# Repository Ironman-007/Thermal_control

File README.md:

# Thermal_control

Due to my research, I always need to measure, log, and control the temperature of the environment during some experiment, such as TVAC test, etc. So I think it would be great to have a standard Kit to do this.
I made this for my personal usage, with 4 channels of RTD to measure temeprature and 4 channels of heater control.

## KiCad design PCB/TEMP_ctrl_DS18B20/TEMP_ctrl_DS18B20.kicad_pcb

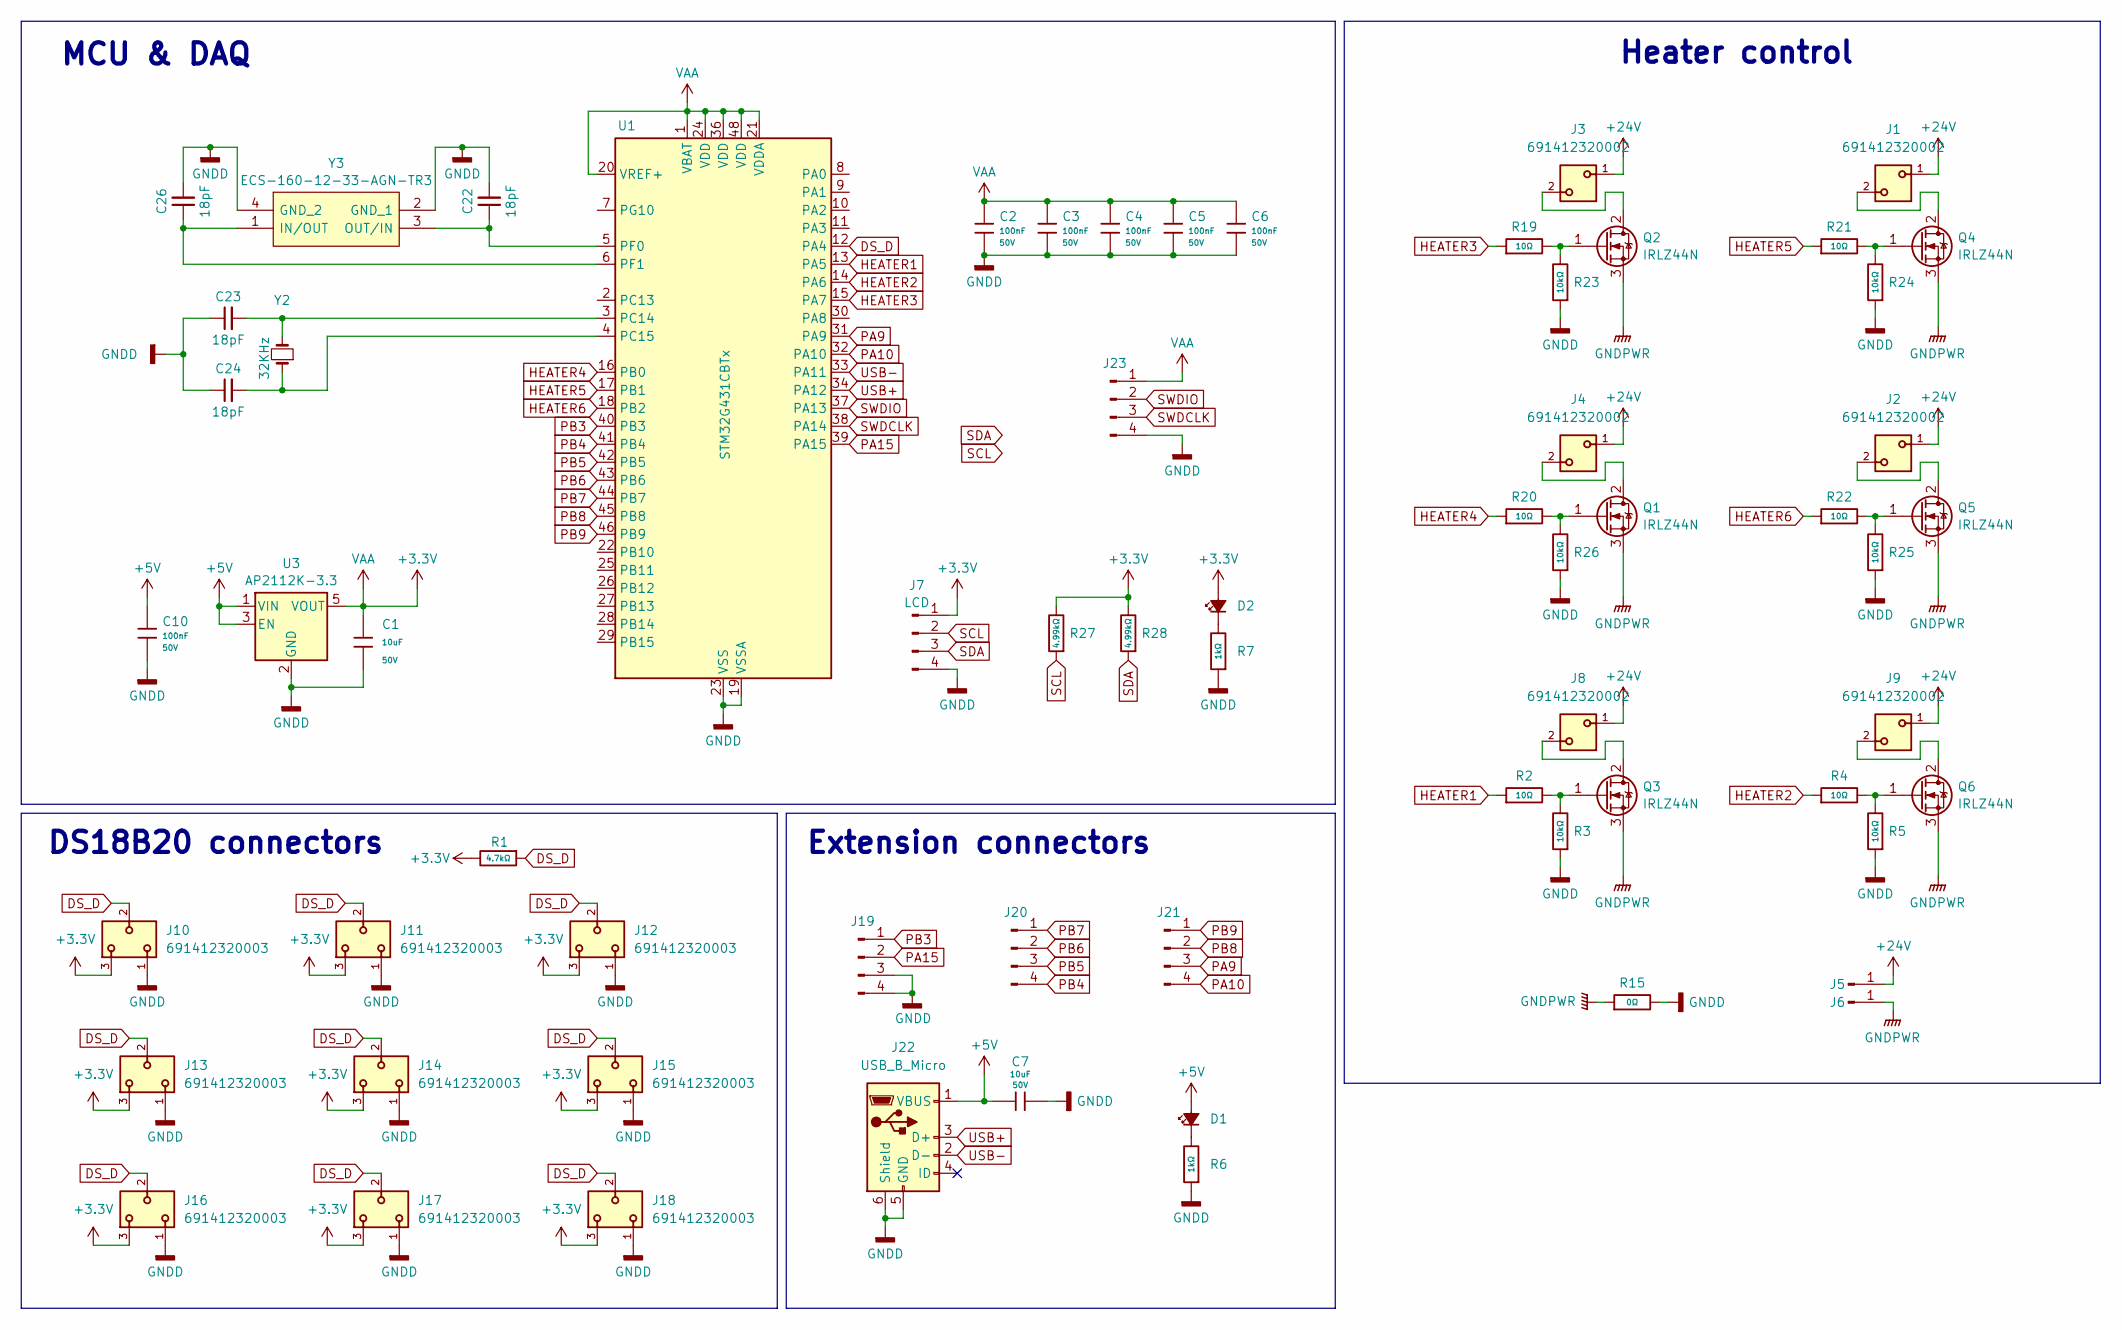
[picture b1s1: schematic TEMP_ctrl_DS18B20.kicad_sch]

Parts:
C1, C7: 10uF; C_1206; Voltage Rated 50V; Tolerance ±10%; Part CL31B104KBCNNNC; LCSC C24497
C2, C3, C4, C5, C6, C10: 100nF; C_0603_1608Metric; Voltage Rated 50V; Tolerance ±10%; Part CL31B104KBCNNNC; LCSC C24497
C22, C23, C24, C26: 18pF; C_0402_1005Metric_Pad0.74x0.62mm_HandSolder
D1, D2: LED_Small_Filled; LED_1206_3216Metric
J1, J2, J3, J4, J8, J9: 691412320002
J5, J6: Conn_01x01_Pin; TestPoint_Pad_4.0x4.0mm
J7: LCD; PinHeader_1x04_P2.54mm_Vertical
J10, J11, J12, J13, J14, J15, J16, J17, J18: 691412320003
J19, J20, J21, J23: Conn_01x04_Pin; PinHeader_1x04_P2.54mm_Vertical
J22: USB_B_Micro; USB_Micro-B_Amphenol_10104110_Horizontal
Q1, Q2, Q3, Q4, Q5, Q6: IRLZ44N; TO-220-3_Vertical
R1: 4.7kΩ; R_1206; Overload Voltage (Max) 200V; Tolerance ±1%; Part 1206W4F1001T5E; LCSC C4410
R2, R4, R19, R20, R21, R22: 10Ω; R_1206; Overload Voltage (Max) 200V; Tolerance ±1%; Part 1206W4F1001T5E; LCSC C4410
R3, R5, R23, R24, R25, R26: 10kΩ; R_1206; Overload Voltage (Max) 200V; Tolerance ±1%; Part 1206W4F1001T5E; LCSC C4410
R6, R7: 1kΩ; R_1206; Overload Voltage (Max) 200V; Tolerance ±1%; Part 1206W4F1001T5E; LCSC C4410
R15: 0Ω; R_1206; Overload Voltage (Max) 200V; Tolerance ±1%; Part 1206W4F0000T5E; LCSC C17888
R27, R28: 4.99kΩ; R_1206; Overload Voltage (Max) 200V; Tolerance ±1%; Part 1206W4F1001T5E; LCSC C4410
U1: STM32G431CBTx; LQFP-48_7x7mm_P0.5mm
U3: AP2112K-3.3; SOT-23-5
Y2: 32KHz; Crystal_SMD_3215-2Pin_3.2x1.5mm
Y3: ECS-160-12-33-AGN-TR3; XTAL_ECS-160-12-33-AGN-TR3; Manufacturer_Part_Number ECS-160-12-33-AGN-TR3; Mouser Part Number 520-160-12-33AGN-TR3

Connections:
+3.3V: C1.1, C2.1, C3.1, C4.1, C5.1, C6.1, D2.2 (A), J7.1, J10.3, J11.3, J12.3, J13.3, J14.3, J15.3, J16.3, J17.3, J18.3, J23.1, R1.2, R27.2, R28.2, U1.1 (VBAT), U1.20 (VREF+), U1.21 (VDDA), U1.24 (VDD), U1.36 (VDD), U1.48 (VDD), U3.5 (VOUT)
+5V: C7.1, C10.1, D1.2 (A), J22.1 (VBUS), U3.1 (VIN), U3.3 (EN)
+24V: J1.1, J2.1, J3.1, J4.1, J5.1, J8.1, J9.1
DS_D: J10.2, J11.2, J12.2, J13.2, J14.2, J15.2, J16.2, J17.2, J18.2, R1.1, U1.12 (PA4)
GNDD: C1.2, C2.2, C3.2, C4.2, C5.2, C6.2, C7.2, C10.2, C22.2, C23.1, C24.1, C26.2, J7.4, J10.1, J11.1, J12.1, J13.1, J14.1, J15.1, J16.1, J17.1, J18.1, J19.3, J19.4, J22.5 (GND), J22.6 (Shield), J23.4, R3.1, R5.1, R6.1, R7.1, R15.2, R23.1, R24.1, R25.1, R26.1, U1.19 (VSSA), U1.23 (VSS), U1.35 (VSS), U1.47 (VSS), U3.2 (GND), Y3.2 (GND_1), Y3.4 (GND_2)
GNDPWR: J6.1, Q1.3 (S), Q2.3 (S), Q3.3 (S), Q4.3 (S), Q5.3 (S), Q6.3 (S), R15.1
HEATER1: R2.1, U1.13 (PA5)
HEATER2: R4.1, U1.14 (PA6)
HEATER3: R19.1, U1.15 (PA7)
HEATER4: R20.1, U1.16 (PB0)
HEATER5: R21.1, U1.17 (PB1)
HEATER6: R22.1, U1.18 (PB2)
unnamed: D1.1 (K), R6.2
unnamed: D2.1 (K), R7.2
unnamed: J4.2, Q1.2 (D)
unnamed: Q1.1 (G), R20.2, R26.2
unnamed: J3.2, Q2.2 (D)
unnamed: Q2.1 (G), R19.2, R23.2
unnamed: J8.2, Q3.2 (D)
unnamed: Q3.1 (G), R2.2, R3.2
unnamed: J1.2, Q4.2 (D)
unnamed: Q4.1 (G), R21.2, R24.2
unnamed: J2.2, Q5.2 (D)
unnamed: Q5.1 (G), R22.2, R25.2
unnamed: J9.2, Q6.2 (D)
unnamed: Q6.1 (G), R4.2, R5.2
unnamed: C23.2, U1.3 (PC14), Y2.2
unnamed: C24.2, U1.4 (PC15), Y2.1
unnamed: C22.1, U1.5 (PF0), Y3.3 (OUT/IN)
unnamed: C26.1, U1.6 (PF1), Y3.1 (IN/OUT)
PA9: J21.3, U1.31 (PA9)
PA10: J21.4, U1.32 (PA10)
PA15: J19.2, U1.39 (PA15)
PB3: J19.1, U1.40 (PB3)
PB4: J20.4, U1.41 (PB4)
PB5: J20.3, U1.42 (PB5)
PB6: J20.2, U1.43 (PB6)
PB7: J20.1, U1.44 (PB7)
PB8: J21.2, U1.45 (PB8)
PB9: J21.1, U1.46 (PB9)
SCL: J7.2, R27.1
SDA: J7.3, R28.1
SWDCLK: J23.3, U1.38 (PA14)
SWDIO: J23.2, U1.37 (PA13)
USB+: J22.3 (D+), U1.34 (PA12)
USB-: J22.2 (D-), U1.33 (PA11)

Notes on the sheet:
Heater control
DS18B20 connectors
Extension connectors
MCU & DAQ

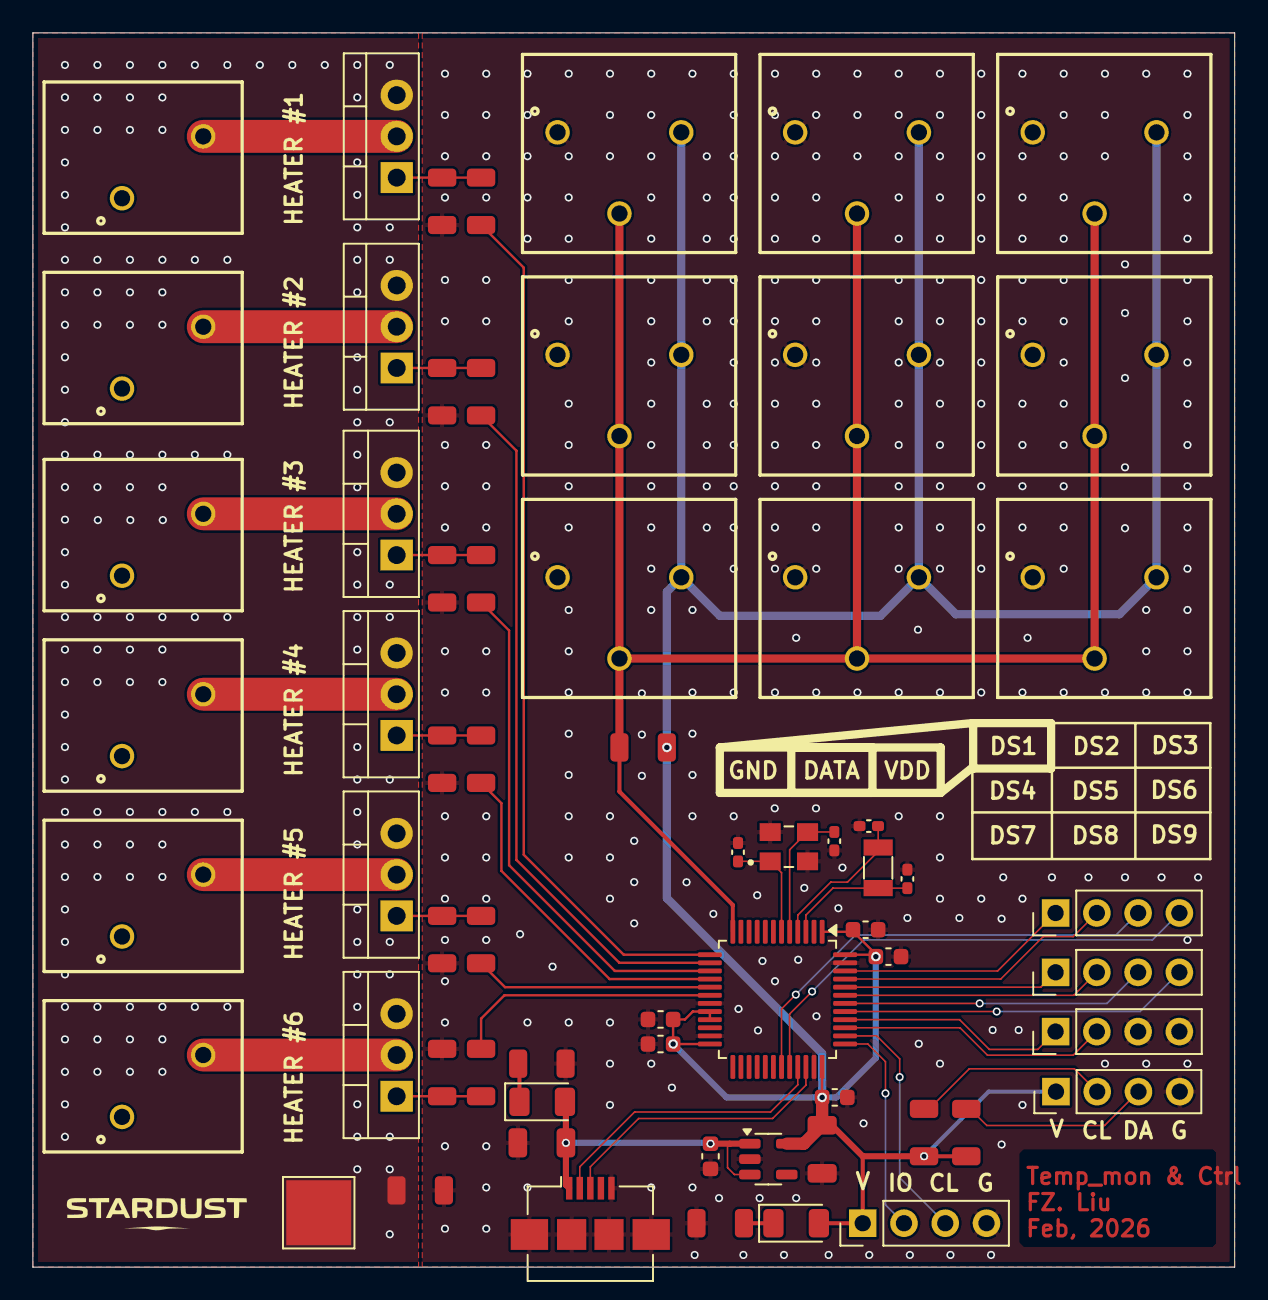
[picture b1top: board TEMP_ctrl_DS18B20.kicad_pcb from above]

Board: 2 copper layers, 74.0 x 76.0 mm, 65 parts (1 on the bottom side), 46 nets.

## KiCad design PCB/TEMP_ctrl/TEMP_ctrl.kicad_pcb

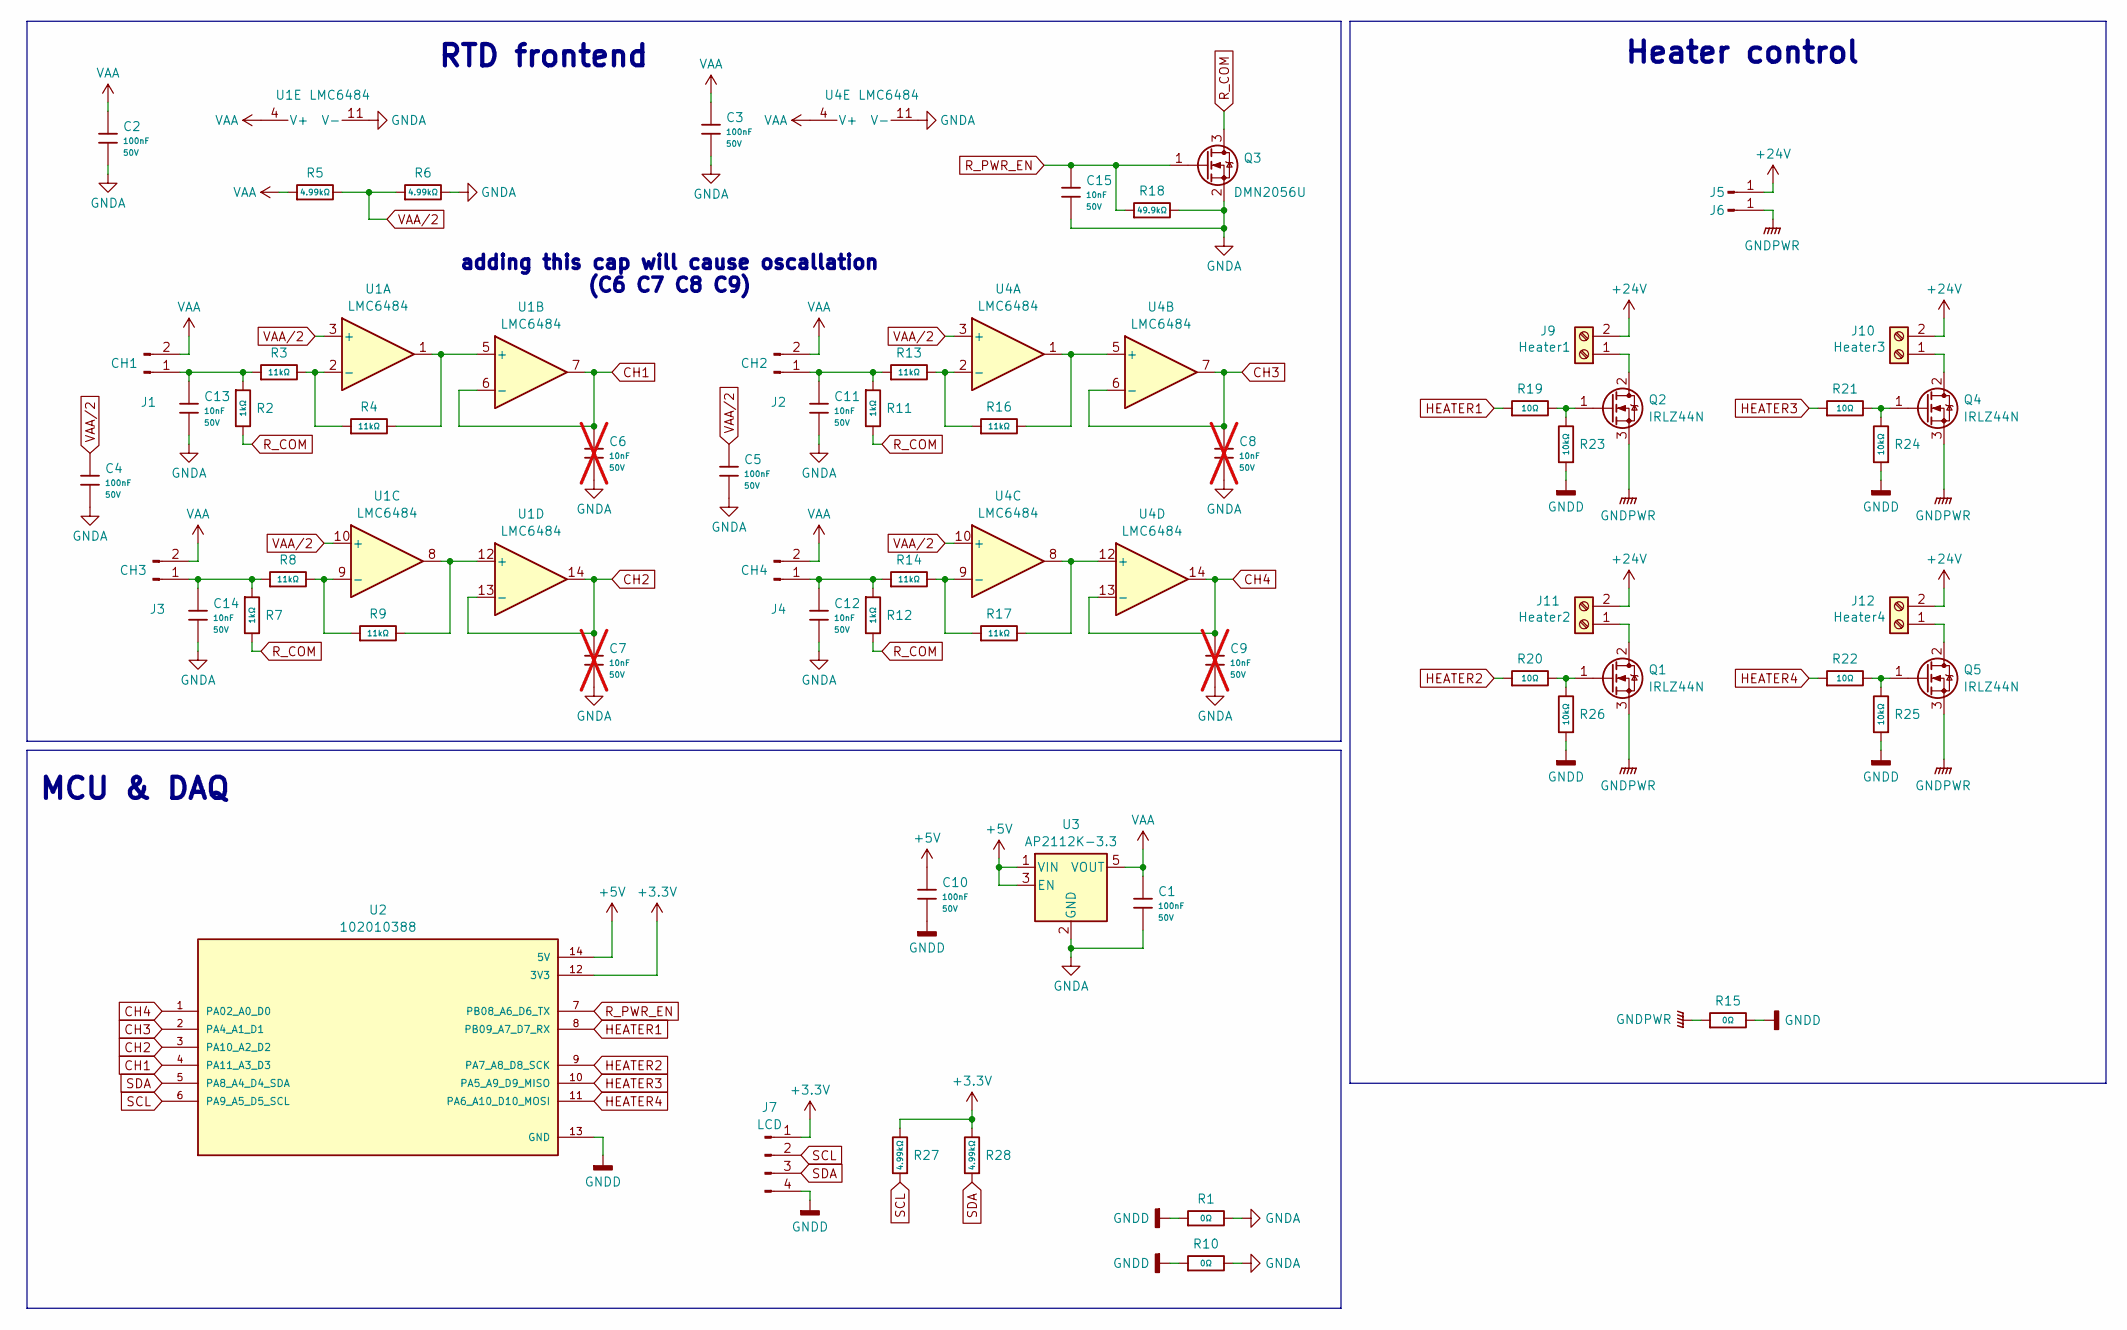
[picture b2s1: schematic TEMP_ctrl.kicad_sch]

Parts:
C1, C2, C3, C4, C5, C10: 100nF; C_1206; Voltage Rated 50V; Tolerance ±10%; Part CL31B104KBCNNNC; LCSC C24497
C6, C7, C8, C9: 10nF; C_1206; Voltage Rated 50V; Tolerance ±10%; Part CL31B104KBCNNNC; LCSC C24497; not fitted
C11, C12, C13, C14, C15: 10nF; C_1206; Voltage Rated 50V; Tolerance ±10%; Part CL31B104KBCNNNC; LCSC C24497
J1: CH1; TerminalBlock_Xinya_XY308-2.54-2P_1x02_P2.54mm_Horizontal
J2: CH2; TerminalBlock_Xinya_XY308-2.54-2P_1x02_P2.54mm_Horizontal
J3: CH3; TerminalBlock_Xinya_XY308-2.54-2P_1x02_P2.54mm_Horizontal
J4: CH4; TerminalBlock_Xinya_XY308-2.54-2P_1x02_P2.54mm_Horizontal
J5, J6: Conn_01x01_Pin; TestPoint_Pad_4.0x4.0mm
J7: LCD; PinHeader_1x04_P2.54mm_Vertical
J9: Heater1; TerminalBlock_MaiXu_MX126-5.0-02P_1x02_P5.00mm
J10: Heater3; TerminalBlock_MaiXu_MX126-5.0-02P_1x02_P5.00mm
J11: Heater2; TerminalBlock_MaiXu_MX126-5.0-02P_1x02_P5.00mm
J12: Heater4; TerminalBlock_MaiXu_MX126-5.0-02P_1x02_P5.00mm
Q1, Q2, Q4, Q5: IRLZ44N; TO-220-3_Vertical
Q3: DMN2056U; SOT-23
R1, R10, R15: 0Ω; R_1206; Overload Voltage (Max) 200V; Tolerance ±1%; Part 1206W4F0000T5E; LCSC C17888
R2, R7, R11, R12: 1kΩ; R_1206; Overload Voltage (Max) 200V; Tolerance ±1%; Part 1206W4F1001T5E; LCSC C4410
R3, R4, R8, R9, R13, R14, R16, R17: 11kΩ; R_1206; Overload Voltage (Max) 200V; Tolerance ±1%; Part 1206W4F1001T5E; LCSC C4410
R5, R6, R27, R28: 4.99kΩ; R_1206; Overload Voltage (Max) 200V; Tolerance ±1%; Part 1206W4F1001T5E; LCSC C4410
R18: 49.9kΩ; R_1206; Overload Voltage (Max) 200V; Tolerance ±1%; Part 1206W4F1001T5E; LCSC C4410
R19, R20, R21, R22: 10Ω; R_1206; Overload Voltage (Max) 200V; Tolerance ±1%; Part 1206W4F1001T5E; LCSC C4410
R23, R24, R25, R26: 10kΩ; R_1206; Overload Voltage (Max) 200V; Tolerance ±1%; Part 1206W4F1001T5E; LCSC C4410
U1, U4: LMC6484; SOIC-14_L8.7-W3.9-P1.27-LS6.0-BL
U2: 102010388; MODULE_102010388; PARTREV N/A
U3: AP2112K-3.3; SOT-23-5

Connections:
+3.3V: J7.1, R27.2, R28.2, U2.12 (3V3)
+5V: C10.1, U2.14 (5V), U3.1 (VIN), U3.3 (EN)
+24V: J5.1, J9.2, J10.2, J11.2, J12.2
CH1: C6.1, U1.6 (-), U1.7, U2.4 (PA11_A3_D3)
CH2: C7.1, U1.13 (-), U1.14, U2.3 (PA10_A2_D2)
CH3: C8.1, U2.2 (PA4_A1_D1), U4.6 (-), U4.7
CH4: C9.1, U2.1 (PA02_A0_D0), U4.13 (-), U4.14
GNDA: C1.2, C2.2, C3.2, C4.2, C5.2, C6.2, C7.2, C8.2, C9.2, C11.2, C12.2, C13.2, C14.2, C15.2, Q3.2 (S), R1.2, R6.2, R10.2, R18.2, U1.11 (V-), U3.2 (GND), U4.11 (V-)
GNDD: C10.2, J7.4, R1.1, R10.1, R15.2, R23.1, R24.1, R25.1, R26.1, U2.13 (GND)
GNDPWR: J6.1, Q1.3 (S), Q2.3 (S), Q4.3 (S), Q5.3 (S), R15.1
HEATER1: R19.1, U2.8 (PB09_A7_D7_RX)
HEATER2: R20.1, U2.9 (PA7_A8_D8_SCK)
HEATER3: R21.1, U2.10 (PA5_A9_D9_MISO)
HEATER4: R22.1, U2.11 (PA6_A10_D10_MOSI)
unnamed: C13.1, J1.1, R2.1, R3.1
unnamed: C11.1, J2.1, R11.1, R13.1
unnamed: C14.1, J3.1, R7.1, R8.1
unnamed: C12.1, J4.1, R12.1, R14.1
unnamed: J9.1, Q2.2 (D)
unnamed: J10.1, Q4.2 (D)
unnamed: J11.1, Q1.2 (D)
unnamed: J12.1, Q5.2 (D)
unnamed: Q1.1 (G), R20.2, R26.2
unnamed: Q2.1 (G), R19.2, R23.2
unnamed: Q4.1 (G), R21.2, R24.2
unnamed: Q5.1 (G), R22.2, R25.2
unnamed: R3.2, R4.1, U1.2 (-)
unnamed: R4.2, U1.1, U1.5 (+)
unnamed: R8.2, R9.1, U1.9 (-)
unnamed: R9.2, U1.8, U1.12 (+)
unnamed: R13.2, R16.1, U4.2 (-)
unnamed: R16.2, U4.1, U4.5 (+)
unnamed: R14.2, R17.1, U4.9 (-)
unnamed: R17.2, U4.8, U4.12 (+)
R_COM: Q3.3 (D), R2.2, R7.2, R11.2, R12.2
R_PWR_EN: C15.1, Q3.1 (G), R18.1, U2.7 (PB08_A6_D6_TX)
SCL: J7.2, R27.1, U2.6 (PA9_A5_D5_SCL)
SDA: J7.3, R28.1, U2.5 (PA8_A4_D4_SDA)
VAA: C1.1, C2.1, C3.1, J1.2, J2.2, J3.2, J4.2, R5.1, U1.4 (V+), U3.5 (VOUT), U4.4 (V+)
VAA/2: C4.1, C5.1, R5.2, R6.1, U1.3 (+), U1.10 (+), U4.3 (+), U4.10 (+)

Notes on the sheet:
Heater control
RTD frontend
adding this cap will cause oscallation (C6 C7 C8 C9)
MCU & DAQ

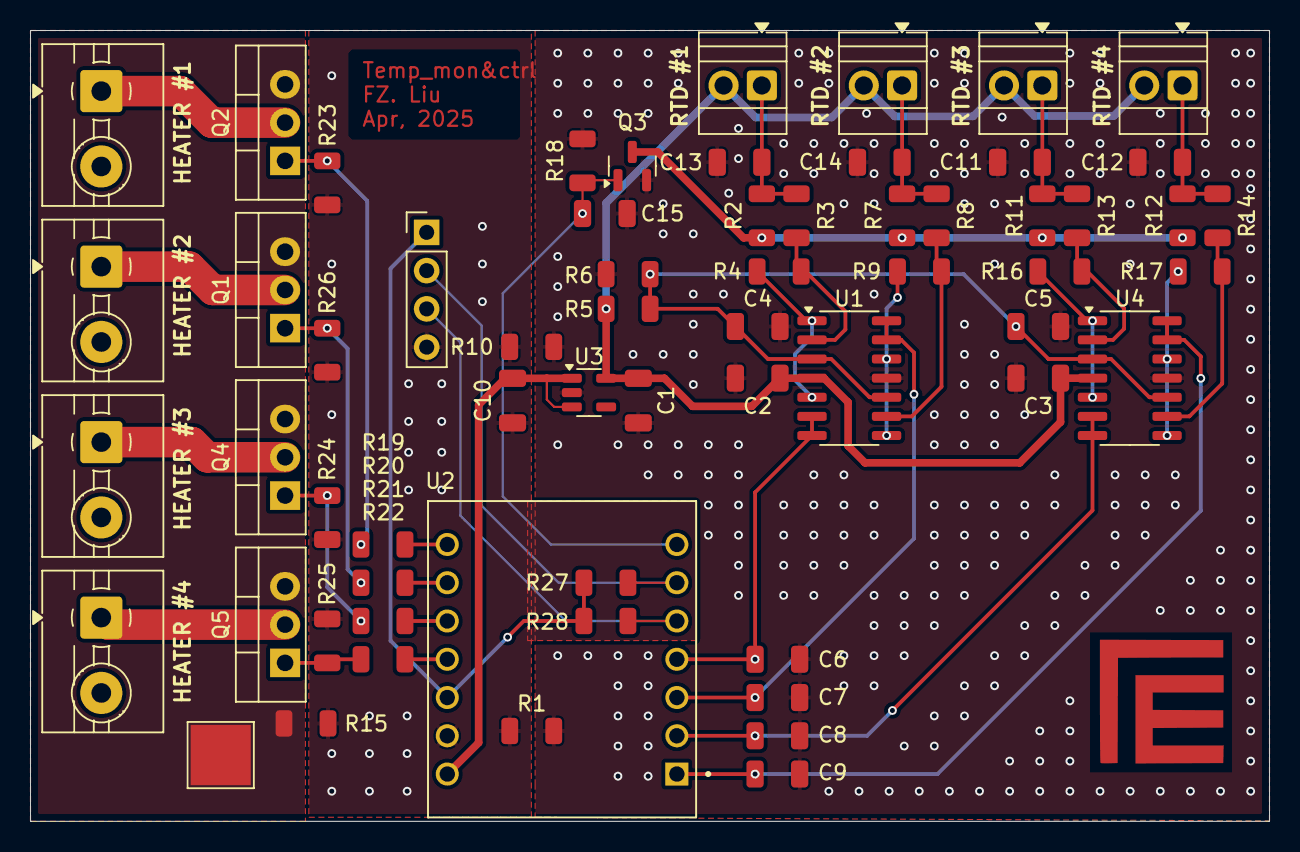
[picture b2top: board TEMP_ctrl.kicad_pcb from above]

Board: 2 copper layers, 82.2 x 52.5 mm, 63 parts (1 on the bottom side), 40 nets.

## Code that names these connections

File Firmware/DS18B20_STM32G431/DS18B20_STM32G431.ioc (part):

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Mcu.Name=STM32G431C(6-8-B)Tx
Mcu.Package=LQFP48
Mcu.UserName=STM32G431CBTx
PA0.Mode=IN1-Single-Ended
PA0.Signal=ADC1_IN1
PA1.Mode=IN2-Single-Ended
PA1.Signal=ADC1_IN2
PA11.Mode=Device
PA11.Signal=USB_DM
PA12.Mode=Device
PA12.Signal=USB_DP
PA13.Mode=Serial_Wire
PA13.Signal=SYS_JTMS-SWDIO
PA14.Mode=Serial_Wire
PA14.Signal=SYS_JTCK-SWCLK
PA2.Mode=IN3-Single-Ended
PA2.Signal=ADC1_IN3
PA3.Mode=IN4-Single-Ended
PA3.Signal=ADC1_IN4
PA4.Mode=IN17-Single-Ended
PA4.Signal=ADC2_IN17
PA5.Mode=IN13-Single-Ended
PA5.Signal=ADC2_IN13
PA6.Mode=IN3-Single-Ended
PA6.Signal=ADC2_IN3
PA7.Mode=IN4-Single-Ended
PA7.Signal=ADC2_IN4
PB11.Mode=IN14-Single-Ended
PB11.Signal=ADC2_IN14
PB15.Mode=IN15-Single-Ended
PB15.Signal=ADC2_IN15
PB2.Mode=IN12-Single-Ended
PB2.Signal=ADC2_IN12
PC14-OSC32_IN.Mode=LSE-External-Oscillator
PC14-OSC32_IN.Signal=RCC_OSC32_IN
PC15-OSC32_OUT.Mode=LSE-External-Oscillator
PC15-OSC32_OUT.Signal=RCC_OSC32_OUT
PF0-OSC_IN.Mode=HSE-External-Oscillator
PF0-OSC_IN.Signal=RCC_OSC_IN
PF1-OSC_OUT.Mode=HSE-External-Oscillator
PF1-OSC_OUT.Signal=RCC_OSC_OUT
RCC.HSE_VALUE=16000000
RCC.SYSCLKFreq_VALUE=96000000
RCC.SYSCLKSource=RCC_SYSCLKSOURCE_PLLCLK
board=custom

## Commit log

2025-04-17 mac: working on the PCB
2025-04-18 pc: working on the PCB
2025-04-18 mac: finished PCB design
2025-05-04 mac: fisnihed RTDs calibration
2025-05-05 mac: PID calculation part working, then I need to send the data to the hardware.
2025-05-05 mac: PID control working.
2025-05-07 mac: create GUI for both thermal control boards
2025-06-05 mac: gui working, using this version
2026-02-16 PC: working on the DS18B20 PCB design
2026-02-18 PC: finished DS18B20 PCB design
